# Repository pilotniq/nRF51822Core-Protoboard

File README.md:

# nRF51822Core-Protoboard
Small prototyping PCB to mount cheap nRF51822-Core BLE modules on

This directory contails Eagle files for a PCB for mounting nRF51822-Core modules on, with prototyping areas.

For more information see the Hackaday project: https://hackaday.io/project/9967-nrf51822-core-protoboard

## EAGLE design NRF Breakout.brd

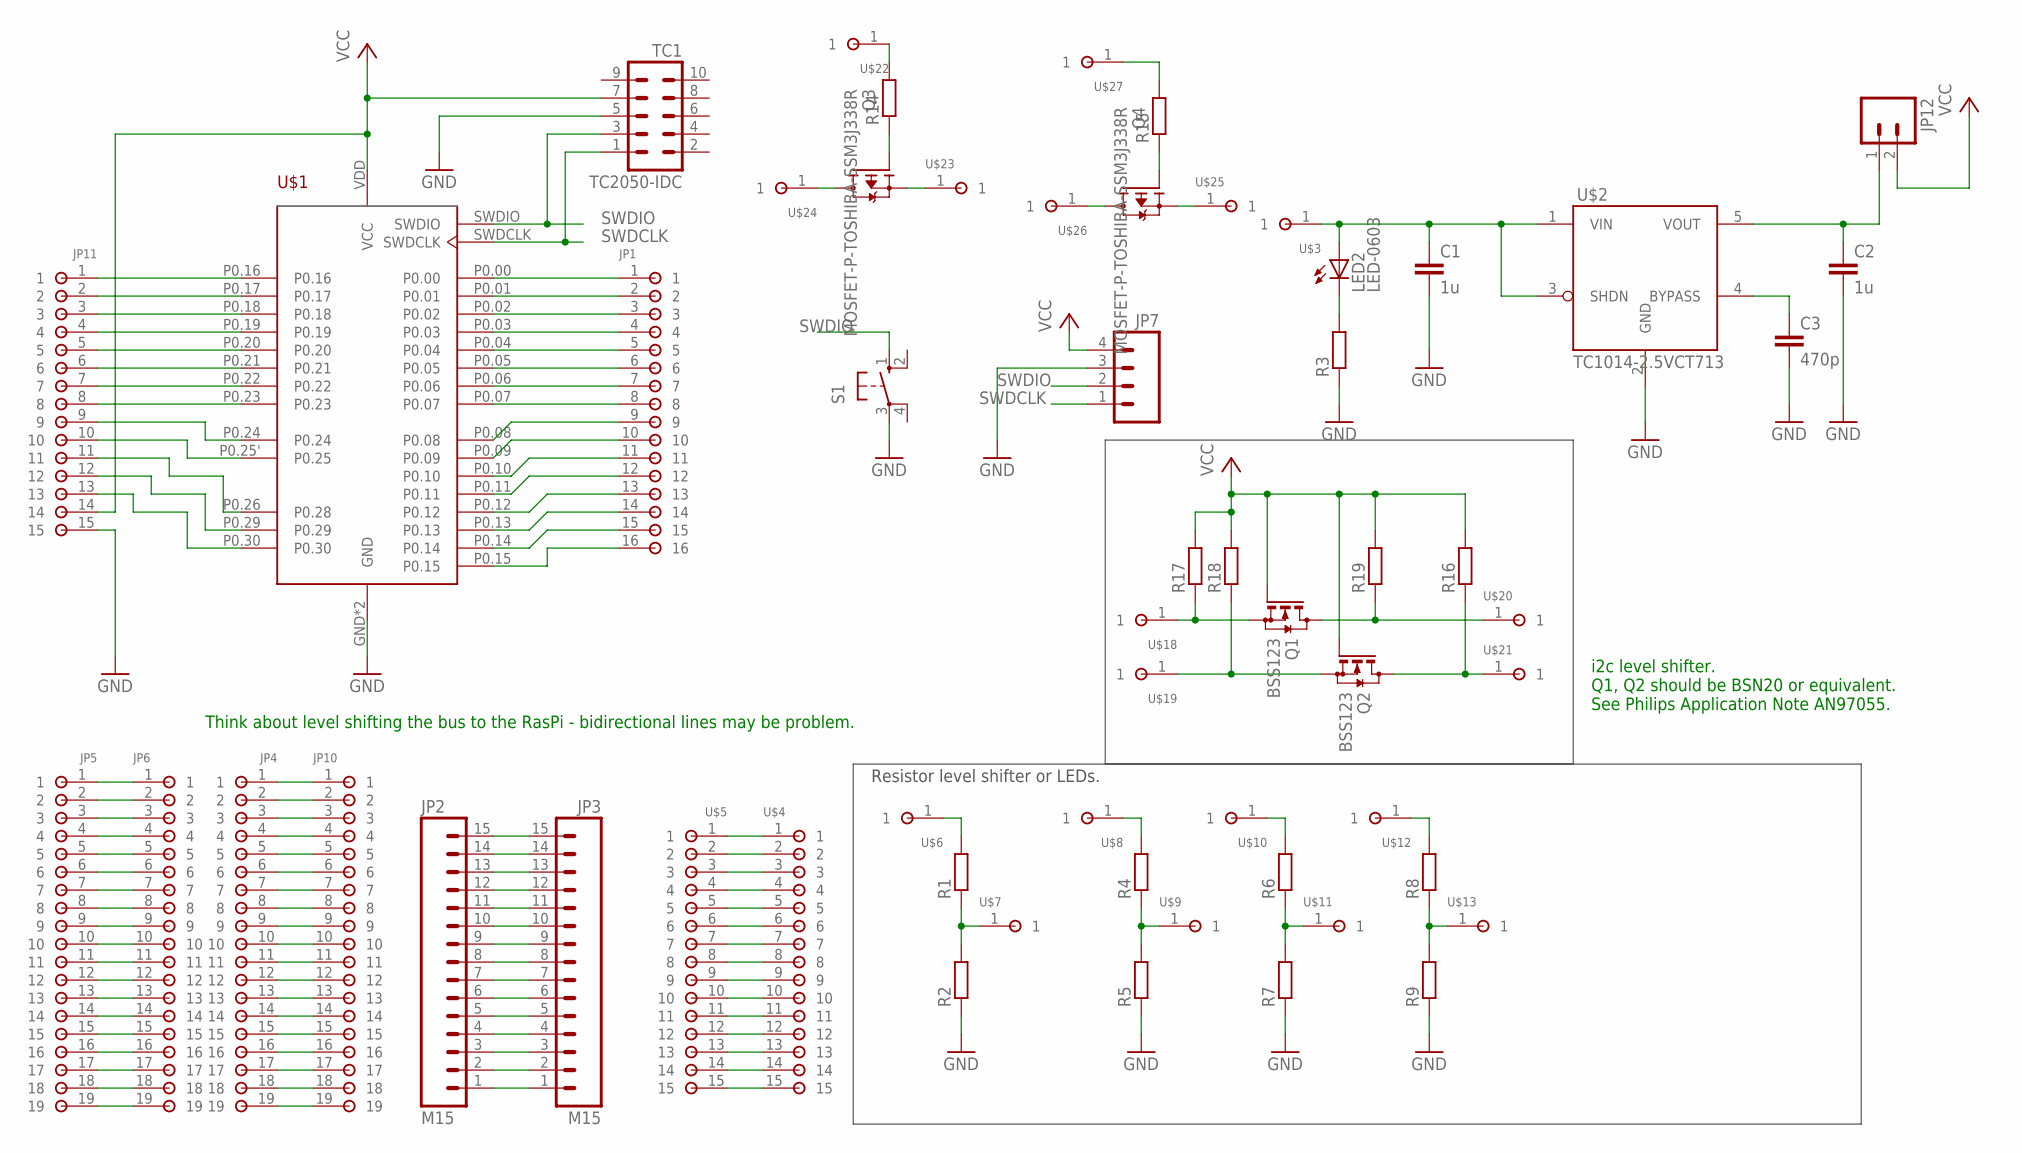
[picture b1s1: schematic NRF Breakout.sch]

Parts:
C1, C2: 1u; C0603
C3: 470p; C0603
JP1: PAD-16-TH
JP2, JP3: M15; 1X15
JP4, JP5, JP6, JP10: PAD-19-2.54-TH
JP7: M04PTH; 1X04
JP11: PAD-15; PAD-15-TH
JP12: M02PTH; 1X02
LED2: LED-0603; CHIPLED_0603
Q1, Q2: BSS123; SOT23
Q3, Q4: MOSFET-P-TOSHIBA-SSM3J338R; SOT23
R1, R2, R3, R4, R5, R6, R7, R8, R9, R14, R15, R16, R17, R18, R19: R-EU_R0603; R0603
S1: TACT-4PIN; B3F-10XX
TC1: TC2050-IDC
U$1: BREAKOUT-NRF51822CORE-SULLINS-NPPN092FFKS-RC; BREAKOUT-NRF51822-CORE-SULLINS-NPPN092FFKS-RC
U$2: TC1014-2.5VCT713; SOT-23-5
U$3, U$6, U$7, U$8, U$9, U$10, U$11, U$12, U$13, U$18, U$19, U$20, U$21, U$22, U$23, U$24, U$25, U$26, U$27: PAD-1-TH
U$4, U$5: PAD-15; PAD-15-TH

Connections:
GND: C1.2, C2.2, C3.2, JP7.3, JP11.15, R2.1, R3.1, R5.1, R7.1, R9.1, S1.3, TC1.5, U$1.GND, U$1.GND2 (GND), U$2.2 (GND)
HIGH1: Q1.3 (D), R19.1, U$20.1
HIGH2: Q2.3 (D), R16.1, U$21.1
LOW1: Q1.2 (S), R17.1, U$18.1
LOW2: Q2.2 (S), R18.1, U$19.1
unnamed: JP2.1, JP3.1
unnamed: C3.1, U$2.4 (BYPASS)
unnamed: R1.2, U$6.1
unnamed: R1.1, R2.2, U$7.1
unnamed: JP5.2, JP6.2
unnamed: JP5.14, JP6.14
unnamed: JP5.3, JP6.3
unnamed: JP5.4, JP6.4
unnamed: JP5.5, JP6.5
unnamed: JP5.6, JP6.6
unnamed: JP5.7, JP6.7
unnamed: JP5.8, JP6.8
unnamed: JP5.9, JP6.9
unnamed: JP5.10, JP6.10
unnamed: JP5.11, JP6.11
unnamed: JP5.12, JP6.12
unnamed: JP5.13, JP6.13
unnamed: JP5.15, JP6.15
unnamed: JP5.16, JP6.16
unnamed: R14.2, U$22.1
unnamed: JP11.2, U$1.P0.17
unnamed: JP11.3, U$1.P0.18
unnamed: JP11.4, U$1.P0.19
unnamed: JP11.5, U$1.P0.20
unnamed: JP1.12, U$1.P0.11
unnamed: JP1.11, U$1.P0.10
unnamed: JP1.13, U$1.P0.12
unnamed: R4.2, U$8.1
unnamed: JP1.6, U$1.P0.05
unnamed: JP1.14, U$1.P0.13
unnamed: JP1.15, U$1.P0.14
unnamed: Q3.1 (G), R14.1
unnamed: JP11.6, U$1.P0.21
unnamed: JP11.7, U$1.P0.22
unnamed: JP11.8, U$1.P0.23
unnamed: JP5.17, JP6.17
unnamed: JP5.18, JP6.18
unnamed: JP5.19, JP6.19
unnamed: JP5.1, JP6.1
unnamed: JP4.19, JP10.19
unnamed: JP4.18, JP10.18
unnamed: JP4.17, JP10.17
unnamed: JP4.16, JP10.16
unnamed: JP4.15, JP10.15
unnamed: JP4.14, JP10.14
unnamed: JP4.13, JP10.13
unnamed: JP4.12, JP10.12
unnamed: JP4.11, JP10.11
unnamed: JP4.10, JP10.10
unnamed: JP4.9, JP10.9
unnamed: JP4.8, JP10.8
unnamed: JP4.7, JP10.7
unnamed: JP4.6, JP10.6
unnamed: JP4.5, JP10.5
unnamed: JP4.4, JP10.4
unnamed: JP4.3, JP10.3
unnamed: JP4.2, JP10.2
unnamed: JP4.1, JP10.1
unnamed: JP2.2, JP3.2
unnamed: JP2.3, JP3.3
unnamed: JP2.4, JP3.4
unnamed: JP2.5, JP3.5
unnamed: JP2.6, JP3.6
unnamed: JP2.7, JP3.7
unnamed: JP2.8, JP3.8
unnamed: JP2.9, JP3.9
unnamed: JP2.10, JP3.10
unnamed: JP2.11, JP3.11
unnamed: JP2.12, JP3.12
unnamed: JP2.13, JP3.13
unnamed: JP2.14, JP3.14
unnamed: JP2.15, JP3.15
unnamed: U$4.1, U$5.1
unnamed: U$4.2, U$5.2
unnamed: U$4.3, U$5.3
unnamed: U$4.4, U$5.4
unnamed: U$4.5, U$5.5
unnamed: U$4.6, U$5.6
unnamed: U$4.7, U$5.7
unnamed: U$4.8, U$5.8
unnamed: U$4.9, U$5.9
unnamed: U$4.10, U$5.10
unnamed: U$4.11, U$5.11
unnamed: U$4.12, U$5.12
unnamed: U$4.13, U$5.13
unnamed: U$4.14, U$5.14
unnamed: U$4.15, U$5.15
unnamed: R4.1, R5.2, U$9.1
unnamed: LED2.C, R3.2
unnamed: R6.2, U$10.1
unnamed: R6.1, R7.2, U$11.1
unnamed: R8.2, U$12.1
unnamed: R8.1, R9.2, U$13.1
unnamed: Q3.3 (D), U$24.1
unnamed: Q3.2 (S), U$23.1
unnamed: R15.2, U$27.1
unnamed: Q4.1 (G), R15.1
unnamed: Q4.2 (S), U$25.1
unnamed: Q4.3 (D), U$26.1
P0.00: JP1.1, U$1.P0.00
P0.01: JP1.2, U$1.P0.01
P0.02: JP1.3, U$1.P0.02
P0.03: JP1.4, U$1.P0.03
P0.04: JP1.5, U$1.P0.04
P0.06: JP1.7, U$1.P0.06
P0.07: JP1.8, U$1.P0.07
P0.08: JP1.9, U$1.P0.08
P0.09: JP1.10, U$1.P0.09
P0.15: JP1.16, U$1.P0.15
P0.16: JP11.1, U$1.P0.16
P0.24: JP11.9, U$1.P0.24
P0.25: JP11.10, U$1.P0.25' (P0.25)
P0.28: JP11.11, U$1.P0.26 (P0.28)
P0.29: JP11.12, U$1.P0.29
P0.30: JP11.13, U$1.P0.30
SWDCLK: JP7.1, TC1.1, U$1.SWDCLK
SWDIO: JP7.2, S1.1 (S), TC1.3, U$1.SWDIO
VCC: JP7.4, JP11.14, JP12.2, Q1.1 (G), Q2.1 (G), R16.2, R17.2, R18.2, R19.2, TC1.7, U$1.VDD (VCC)
VIN: C1.1, LED2.A, U$2.1 (VIN), U$2.3 (SHDN), U$3.1
VOUT: C2.1, JP12.1, U$2.5 (VOUT)

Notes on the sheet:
Think about level shifting the bus to the RasPi - bidirectional lines may be problem.
i2c level shifter. Q1, Q2 should be BSN20 or equivalent. See Philips Application Note AN97055.
Resistor level shifter or LEDs.

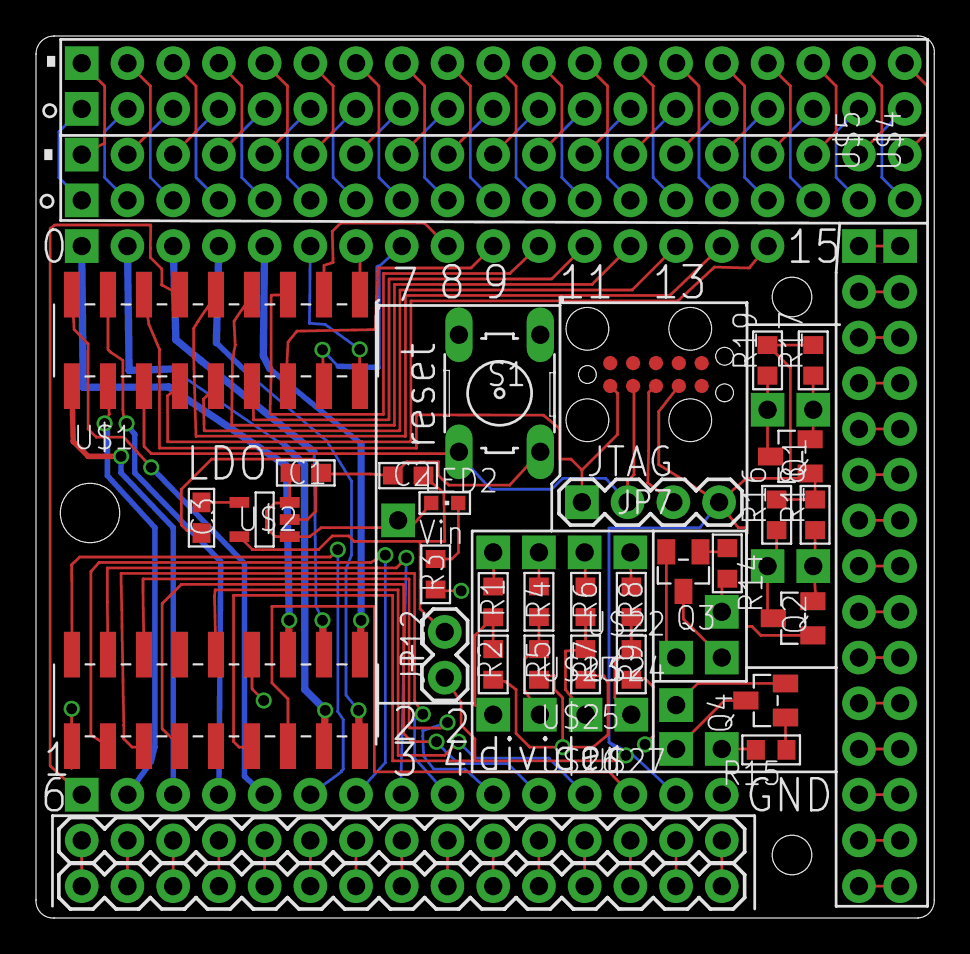
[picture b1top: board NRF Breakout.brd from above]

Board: 2 copper layers, 49.9 x 49.0 mm, 58 parts (0 on the bottom side), 125 nets.

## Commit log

2016-03-03 Initial Check-in, ready for ordering?
2016-03-03 Pushed possible QR code image
2016-03-10 Continued work. This is the version that was ordered from Seeed Studios.

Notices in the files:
parts and their libraries:
SparkFun-Connectors: Licensing: CC v3.0 Share-Alike You are welcome to use this library for commercial purposes.
